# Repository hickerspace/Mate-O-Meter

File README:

Measures our Club-Mate stock with a personal scale connected to an Arduino with ethernet shield.

Check https://hickerspace.org/wiki/Mate-O-Meter for details (German).

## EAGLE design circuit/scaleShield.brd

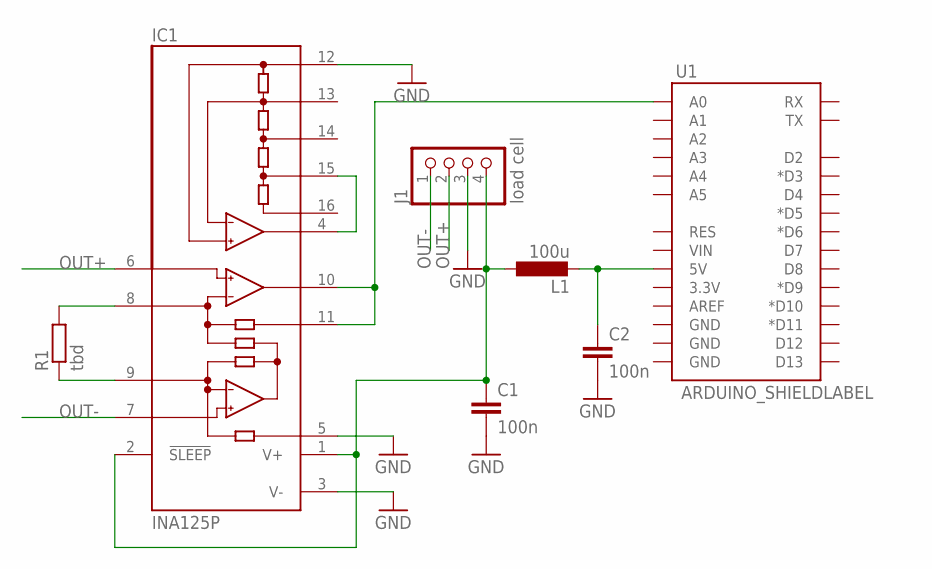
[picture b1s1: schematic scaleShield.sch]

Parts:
C1, C2: 100n; C025-025X050
IC1: INA125P; DIL16
J1: load cell; 1X04
L1: 100u; 0207/10
R1: tbd; 0207/10
U1: ARDUINO_SHIELDLABEL; DUEMILANOVE_SHIELD

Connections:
GND: C1.2, C2.2, IC1.3 (V-), IC1.5 (REF), IC1.12 (REFCOM), J1.3
unnamed: IC1.10 (OUT), IC1.11 (SENSE), U1.A0
unnamed: C2.1, L1.2, U1.5V
unnamed: IC1.4 (REFOUT), IC1.15 (REF5)
unnamed: IC1.8 (RG), R1.2
unnamed: IC1.9 (RG), R1.1
OUT+: IC1.6 (+IN), J1.2
OUT-: IC1.7 (-IN), J1.1
WIRE: C1.1, IC1.1 (V+), IC1.2 (!SLEEP), J1.4, L1.1

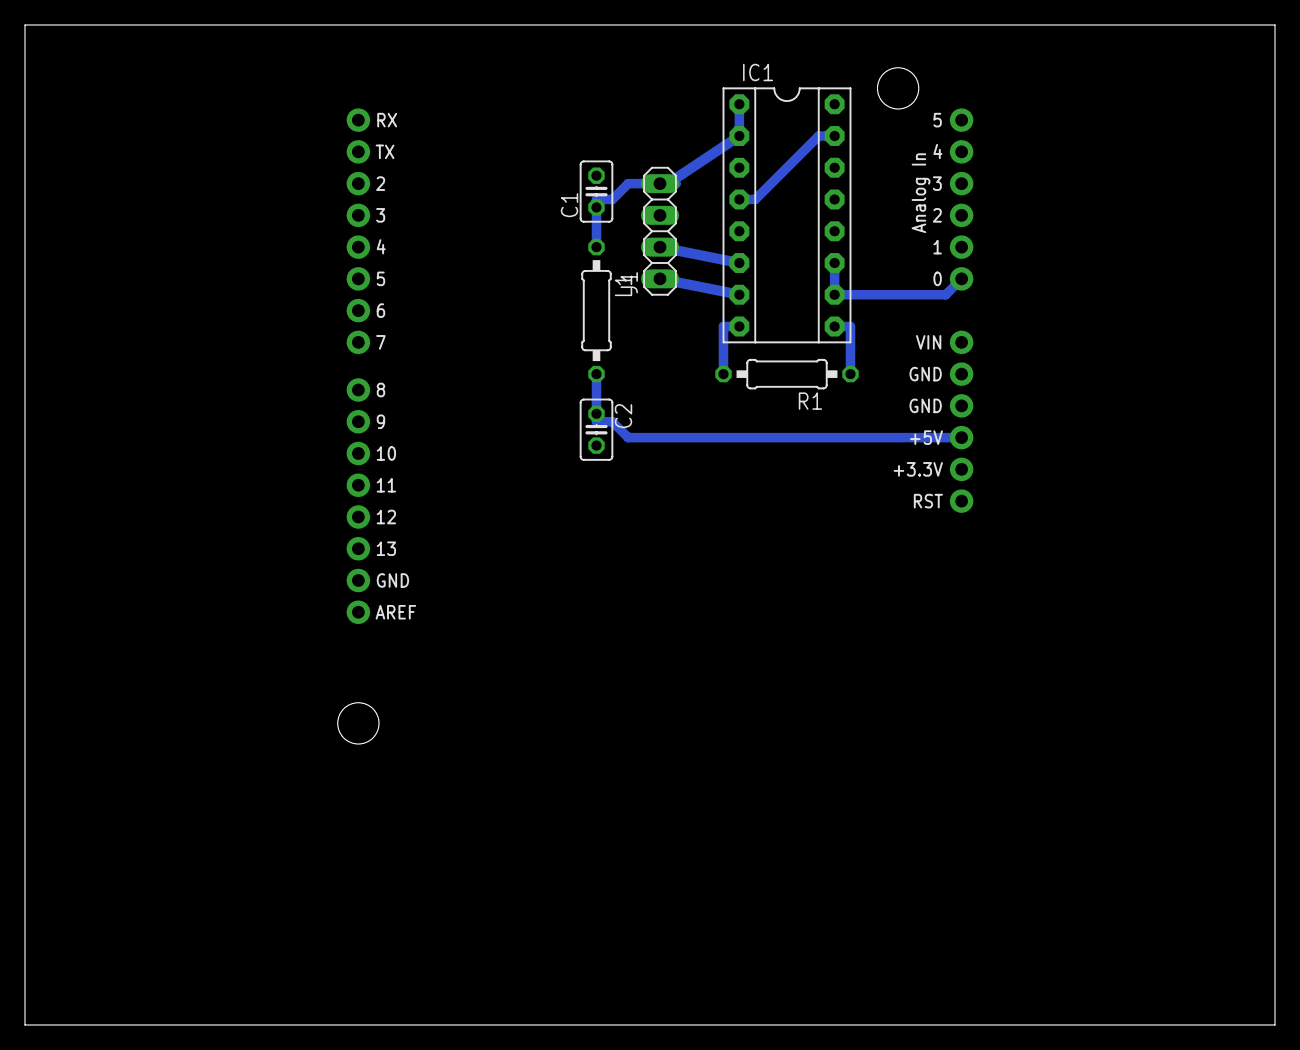
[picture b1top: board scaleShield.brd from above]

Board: 2 copper layers, 100.0 x 80.0 mm, 7 parts (0 on the bottom side), 9 nets.

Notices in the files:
parts and their libraries:
SparkFun-Boards: Licensing: CC v3.0 Share-Alike You are welcome to use this library for commercial purposes.
